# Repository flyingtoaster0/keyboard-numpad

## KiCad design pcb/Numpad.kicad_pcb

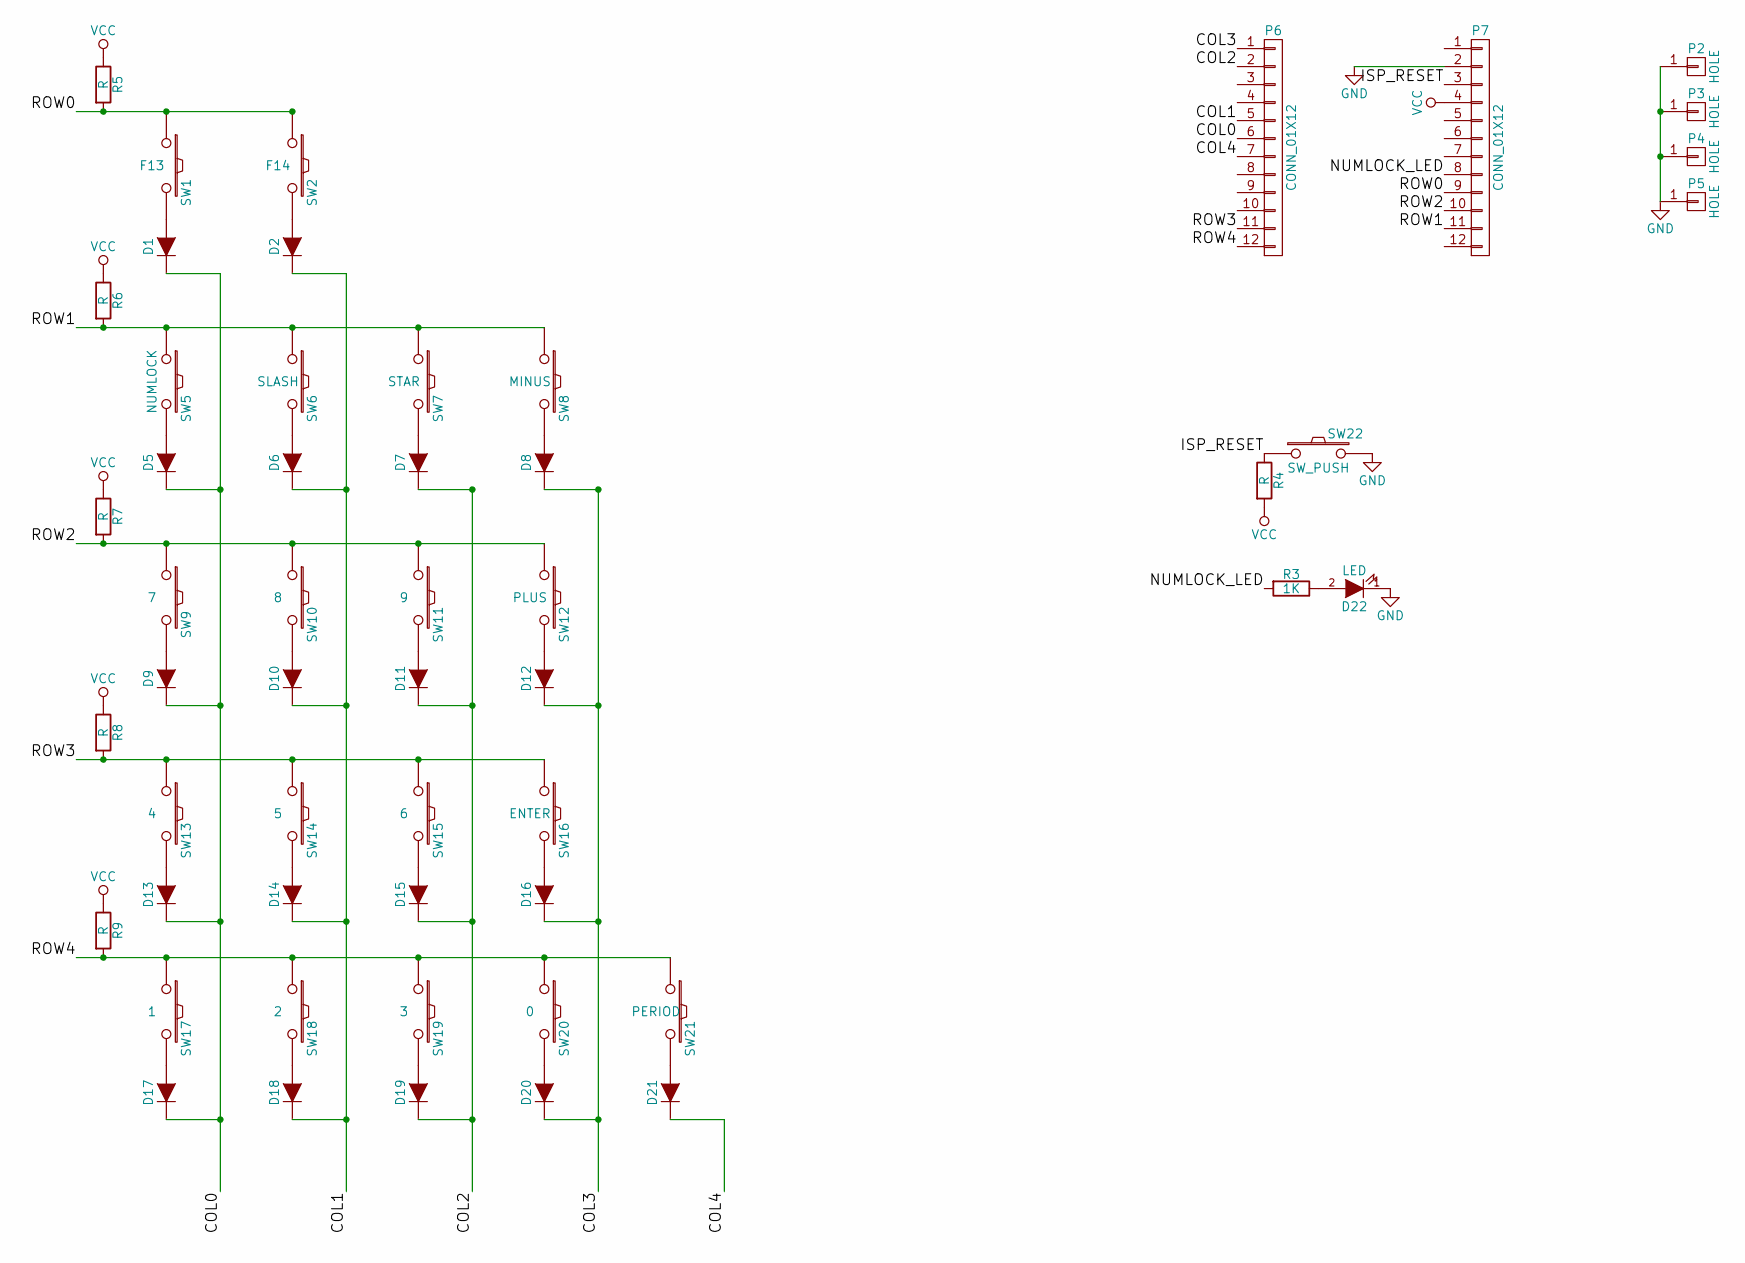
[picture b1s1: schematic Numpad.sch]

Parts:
D1, D2, D5, D6, D7, D8, D9, D10, D11, D12, D13, D14, D15, D16, D17, D18, D19, D20, D21: D; SOD-123
D22: LED; CHERRY_MX_LED
P2, P3, P4, P5: HOLE; 1pin
P6, P7: CONN_01X12; Pin_Header_Straight_1x12_Pitch2.54mm
R3: 1K; R_0805
R4, R5, R6, R7, R8, R9: R; R_0805
SW1: F13; CHERRY_PLATE_100H
SW2: F14; CHERRY_PLATE_100H
SW5: NUMLOCK; CHERRY_PLATE_100H
SW6: SLASH; CHERRY_PLATE_100H
SW7: STAR; CHERRY_PLATE_100H
SW8: MINUS; CHERRY_PLATE_100H
SW9: 7; CHERRY_PLATE_100H
SW10: 8; CHERRY_PLATE_100H
SW11: 9; CHERRY_PLATE_100H
SW12: PLUS; CHERRY_PLATE_200V
SW13: 4; CHERRY_PLATE_100H
SW14: 5; CHERRY_PLATE_100H
SW15: 6; CHERRY_PLATE_100H
SW16: ENTER; CHERRY_PLATE_200V
SW17: 1; CHERRY_PLATE_100H
SW18: 2; CHERRY_PLATE_100H
SW19: 3; CHERRY_PLATE_100H
SW20: 0; CHERRY_PLATE_200H
SW21: PERIOD; CHERRY_PLATE_100H
SW22: SW_PUSH; SW_SPST_B3S-1000

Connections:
/COL0: D1.1 (K), D5.1 (K), D9.1 (K), D13.1 (K), D17.1 (K), P6.6
/COL1: D2.1 (K), D6.1 (K), D10.1 (K), D14.1 (K), D18.1 (K), P6.5
/COL2: D7.1 (K), D11.1 (K), D15.1 (K), D19.1 (K), P6.2
/COL3: D8.1 (K), D12.1 (K), D16.1 (K), D20.1 (K), P6.1
/COL4: D21.1 (K), P6.7
/ISP_RESET: P7.3, R4.1, SW22.1
/NUMLOCK_LED: P7.8, R3.2
/ROW0: P7.9, R5.2, SW1.1, SW2.1
/ROW1: P7.11, R6.2, SW5.1, SW6.1, SW7.1, SW8.1
/ROW2: P7.10, R7.2, SW9.1, SW10.1, SW11.1, SW12.1
/ROW3: P6.11, R8.2, SW13.1, SW14.1, SW15.1, SW16.1
/ROW4: P6.12, R9.2, SW17.1, SW18.1, SW19.1, SW20.1, SW21.1
GND: D22.1 (K), P2.1, P3.1, P4.1, P5.1, P7.2, SW22.2
unnamed: D1.2 (A), SW1.2
unnamed: D2.2 (A), SW2.2
unnamed: D5.2 (A), SW5.2
unnamed: D6.2 (A), SW6.2
unnamed: D7.2 (A), SW7.2
unnamed: D8.2 (A), SW8.2
unnamed: D9.2 (A), SW9.2
unnamed: D10.2 (A), SW10.2
unnamed: D11.2 (A), SW11.2
unnamed: D12.2 (A), SW12.2
unnamed: D13.2 (A), SW13.2
unnamed: D14.2 (A), SW14.2
unnamed: D15.2 (A), SW15.2
unnamed: D16.2 (A), SW16.2
unnamed: D17.2 (A), SW17.2
unnamed: D18.2 (A), SW18.2
unnamed: D19.2 (A), SW19.2
unnamed: D20.2 (A), SW20.2
unnamed: D21.2 (A), SW21.2
unnamed: D22.2 (A), R3.1
VCC: P7.4, R4.2, R5.1, R6.1, R7.1, R8.1, R9.1

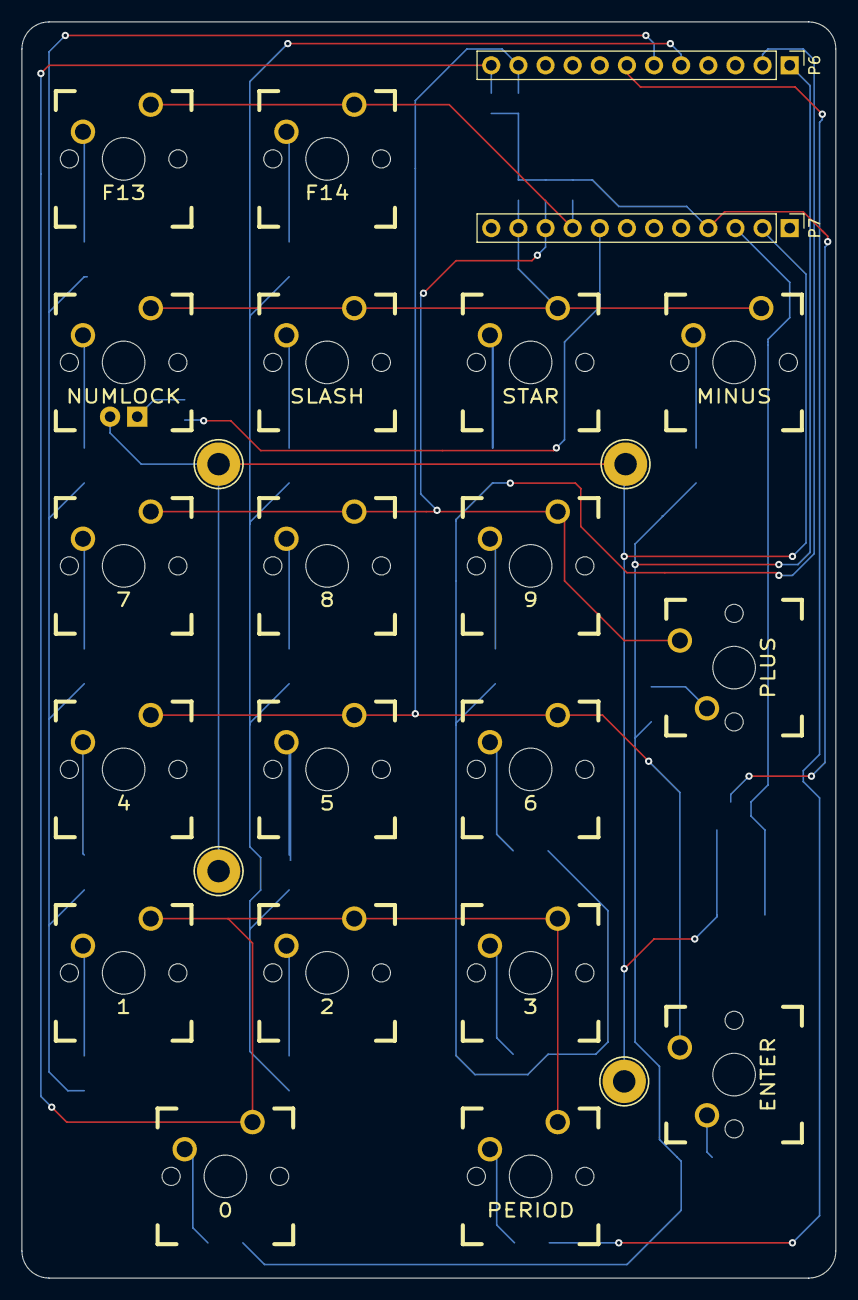
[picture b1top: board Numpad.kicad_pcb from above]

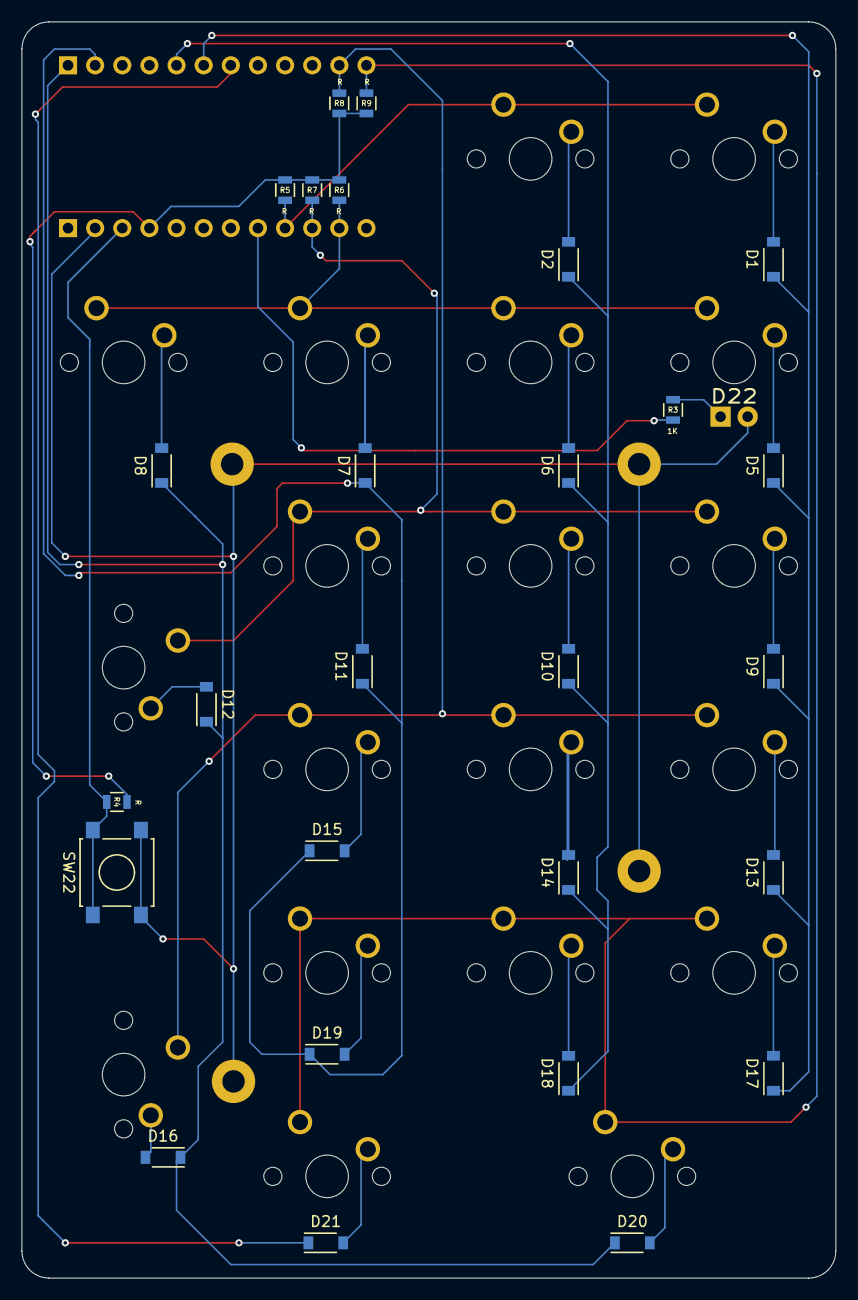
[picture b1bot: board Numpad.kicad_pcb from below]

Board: 2 copper layers, 76.2 x 117.6 mm, 53 parts (27 on the bottom side), 34 nets.

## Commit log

2016-09-14 Move project into directory
2016-09-14 Add some code files. Not all of them. Just the interesting ones for now
2016-12-01 Update schematic
2016-12-01 Start laying out the PCB
2016-12-01 Lay out components mostly
2016-12-01 Add SMD micro USB B, move MCU
2016-12-02 Add OSH Park design rules
2016-12-02 Add the cache .lib
2016-12-02 Add mounting holes to schematic
2016-12-02 Fix mounting hole names
2016-12-02 Associate holes with footprints
2016-12-02 Add holes to pcb
2016-12-02 Try routing one row, one column
2016-12-02 Routing
2016-12-02 Accidentally did most of the routing
2016-12-02 Finish routing
2016-12-02 Add edge cuts
2016-12-02 **ROUNDED** edge cuts :D
2016-12-02 Add my own key footprints
2016-12-04 move drill hole
2016-12-04 Make drill holes 2.1mm diameter
2017-01-10 Fix VCC/+5V problem. Shrink board by like 10 mils
2017-01-10 Macrofab order
2017-04-21 Remove atmega32u4 and related components
2017-04-21 Complete routes and layout. Need to check Osh Park rules
2017-04-22 fix track widths for Osh Park
2017-04-22 Wire up Numlock LED
2017-05-04 Change wires to match prototype, add pullups for columns
2017-05-05 fix a track
